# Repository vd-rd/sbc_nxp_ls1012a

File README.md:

# sbc-ls1012a
NXP Layerscape LS1012A

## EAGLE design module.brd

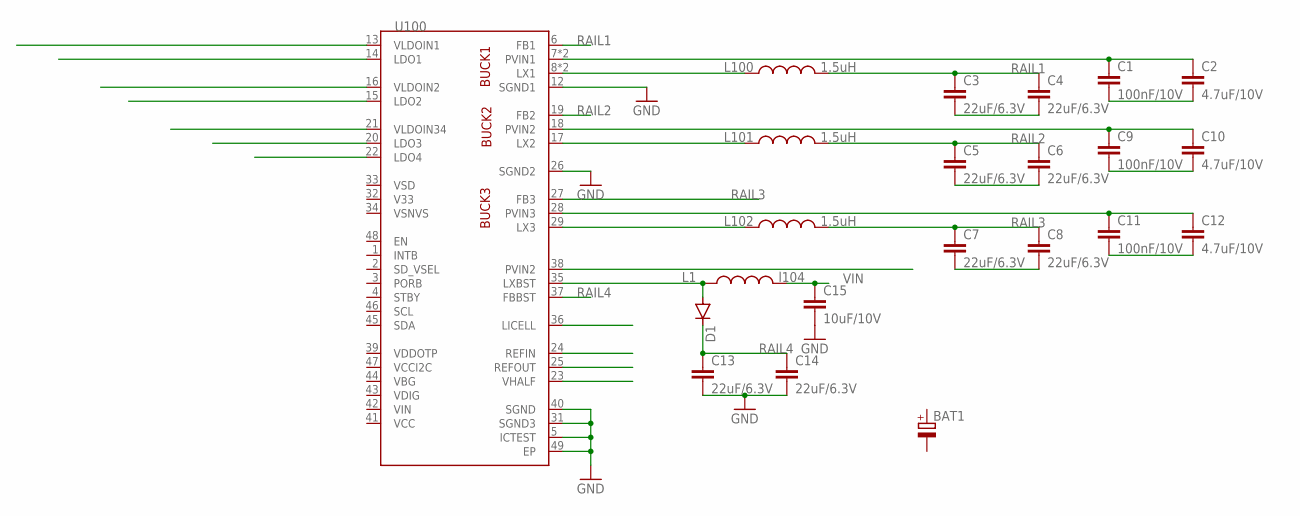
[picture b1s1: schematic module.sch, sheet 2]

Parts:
BAT1: DCK-3R3E224U-E; 621
C1, C9, C11: 100nF/10V; C0603
C2, C10, C12: 4.7uF/10V; C0603
C3, C4, C5, C6, C7, C8, C13, C14: 22uF/6.3V; C0805
C15: 10uF/10V; C0805
D1: DIODE-SOD123; SOD123
L1: l104; INDPM5552X300N
L100, L101, L102: 1.5uH; INDPM5552X300N
U100: MC34VR5100A1EP; QFN50P700X700X90-49T410N

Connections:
GND: C13.2, C14.2, C15.2, U100.5 (ICTEST), U100.12 (SGND1), U100.26 (SGND2), U100.31 (SGND3), U100.40 (SGND), U100.49 (EP)
unnamed: L100.1, U100.8 (LX1), U100.9 (LX1)
unnamed: C1.1, C2.1, U100.7 (PVIN1), U100.10 (PVIN1)
unnamed: L101.1, U100.17 (LX2)
unnamed: L102.1, U100.29 (LX3)
unnamed: D1.A, L1.1, U100.35 (LXBST)
unnamed: C9.1, C10.1, U100.18 (PVIN2)
unnamed: C11.1, C12.1, U100.28 (PVIN3)
unnamed: C3.2, C4.2
unnamed: C1.2, C2.2
unnamed: C11.2, C12.2
unnamed: C7.2, C8.2
unnamed: C5.2, C6.2
unnamed: C9.2, C10.2
RAIL1: C3.1, C4.1, L100.2, U100.6 (FB1)
RAIL2: C5.1, C6.1, L101.2, U100.19 (FB2)
RAIL3: C7.1, C8.1, L102.2, U100.27 (FB3)
RAIL4: C13.1, C14.1, D1.C, U100.37 (FBBST)
VIN: C15.1, L1.2

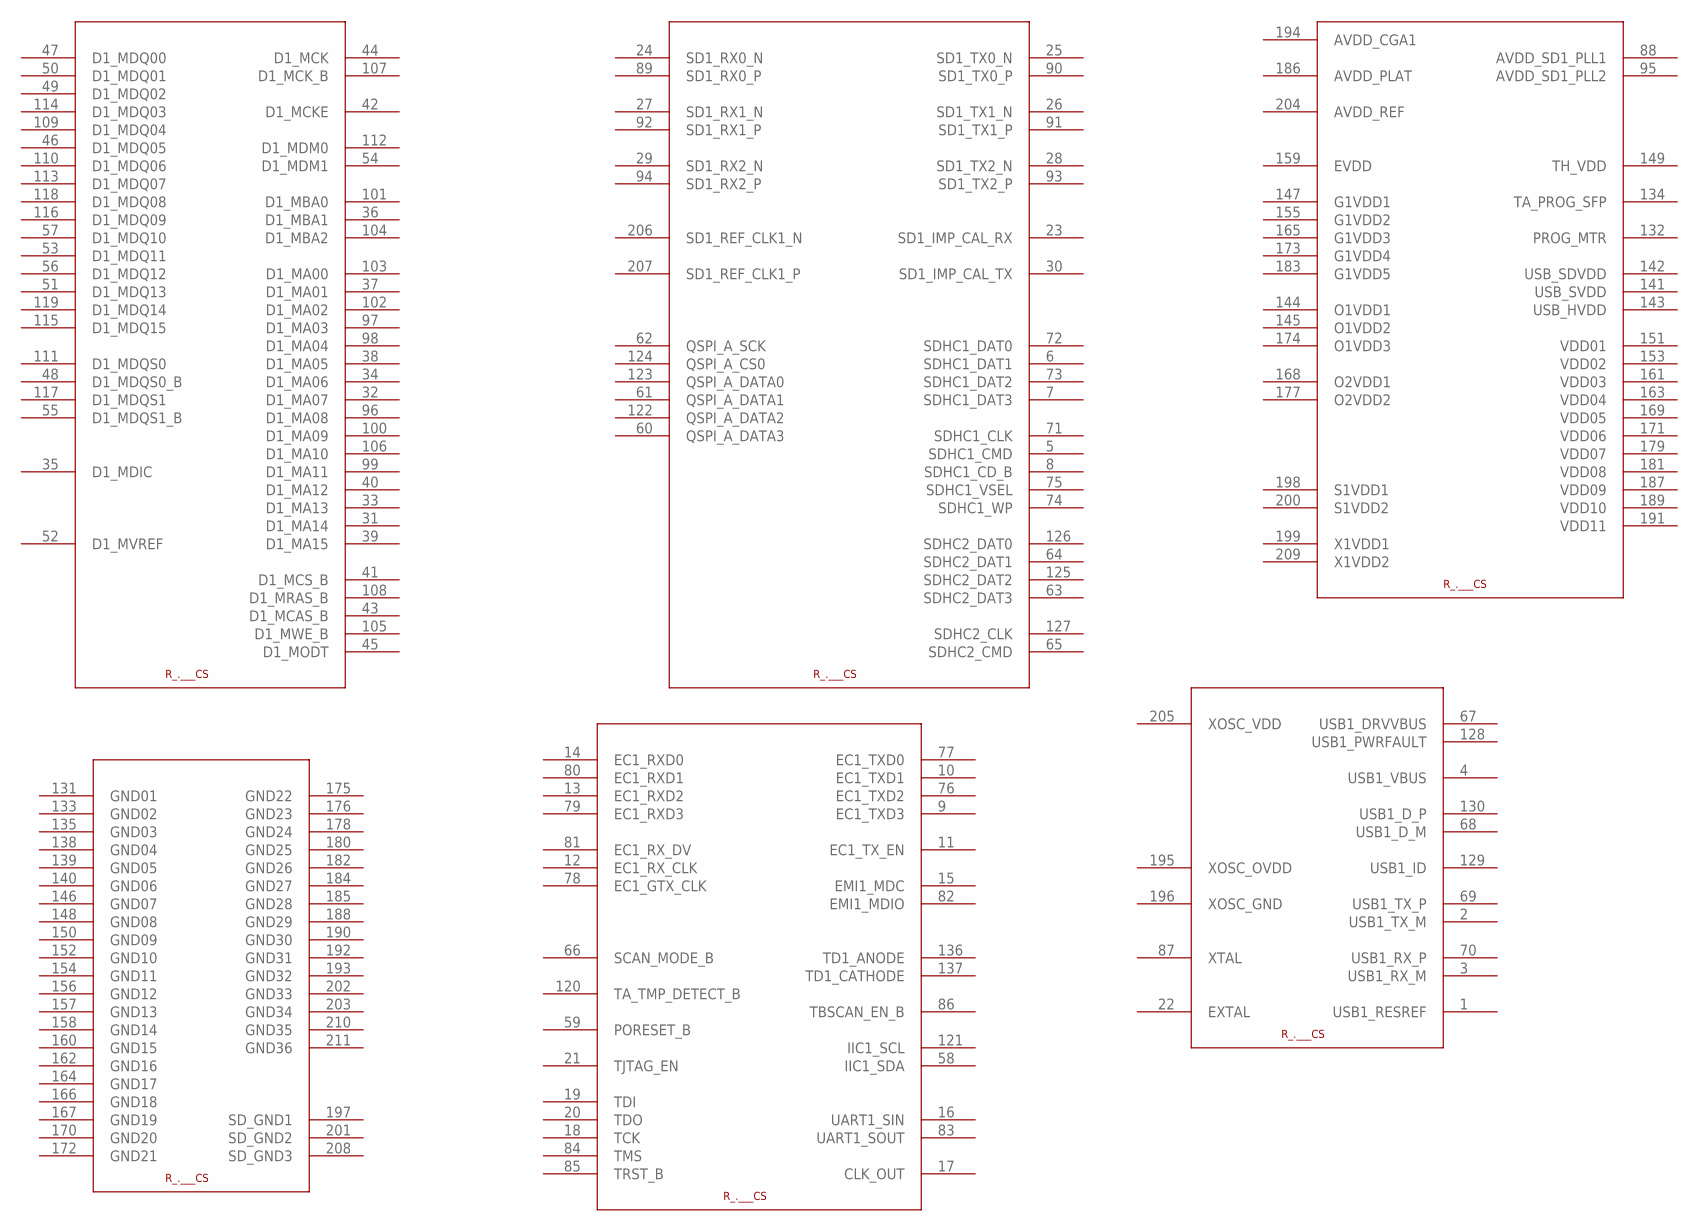
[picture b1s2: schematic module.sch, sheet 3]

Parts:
U3: LS1012ASE7EKA; NXP_LS1012ASE7EKA

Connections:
AVDD_CGA1: U3.194 (AVDD_CGA1)
AVDD_PLAT: U3.186 (AVDD_PLAT)
AVDD_REF: U3.204 (AVDD_REF)
AVDD_SD1_PLL1: U3.88 (AVDD_SD1_PLL1)
AVDD_SD1_PLL2: U3.95 (AVDD_SD1_PLL2)
EVDD: U3.159 (EVDD)
G1VDD1: U3.147 (G1VDD1)
G1VDD2: U3.155 (G1VDD2)
G1VDD3: U3.165 (G1VDD3)
G1VDD4: U3.173 (G1VDD4)
G1VDD5: U3.183 (G1VDD5)
GND01: U3.131 (GND01)
GND02: U3.133 (GND02)
GND03: U3.135 (GND03)
GND04: U3.138 (GND04)
GND05: U3.139 (GND05)
GND06: U3.140 (GND06)
GND07: U3.146 (GND07)
GND08: U3.148 (GND08)
GND09: U3.150 (GND09)
GND10: U3.152 (GND10)
GND11: U3.154 (GND11)
GND12: U3.156 (GND12)
GND13: U3.157 (GND13)
GND14: U3.158 (GND14)
GND15: U3.160 (GND15)
GND16: U3.162 (GND16)
GND17: U3.164 (GND17)
GND18: U3.166 (GND18)
GND19: U3.167 (GND19)
GND20: U3.170 (GND20)
GND21: U3.172 (GND21)
GND22: U3.175 (GND22)
GND23: U3.176 (GND23)
GND24: U3.178 (GND24)
GND25: U3.180 (GND25)
GND26: U3.182 (GND26)
GND27: U3.184 (GND27)
GND28: U3.185 (GND28)
GND29: U3.188 (GND29)
GND30: U3.190 (GND30)
GND31: U3.192 (GND31)
GND32: U3.193 (GND32)
GND33: U3.202 (GND33)
GND34: U3.203 (GND34)
GND35: U3.210 (GND35)
GND36: U3.211 (GND36)
O1VDD1: U3.144 (O1VDD1)
O1VDD2: U3.145 (O1VDD2)
O1VDD3: U3.174 (O1VDD3)
O2VDD1: U3.168 (O2VDD1)
O2VDD2: U3.177 (O2VDD2)
PROG_MTR: U3.132 (PROG_MTR)
S1VDD1: U3.198 (S1VDD1)
S1VDD2: U3.200 (S1VDD2)
SD_GND1: U3.197 (SD_GND1)
SD_GND2: U3.201 (SD_GND2)
SD_GND3: U3.208 (SD_GND3)
TH_VDD: U3.149 (TH_VDD)
USB_HVDD: U3.143 (USB_HVDD)
USB_SDVDD: U3.142 (USB_SDVDD)
USB_SVDD: U3.141 (USB_SVDD)
VDD01: U3.151 (VDD01)
VDD02: U3.153 (VDD02)
VDD03: U3.161 (VDD03)
VDD04: U3.163 (VDD04)
VDD05: U3.169 (VDD05)
VDD06: U3.171 (VDD06)
VDD07: U3.179 (VDD07)
VDD08: U3.181 (VDD08)
VDD09: U3.187 (VDD09)
VDD10: U3.189 (VDD10)
VDD11: U3.191 (VDD11)
X1VDD1: U3.199 (X1VDD1)
X1VDD2: U3.209 (X1VDD2)
XOSC_GND: U3.196 (XOSC_GND)
XOSC_OVDD: U3.195 (XOSC_OVDD)
XOSC_VDD: U3.205 (XOSC_VDD)

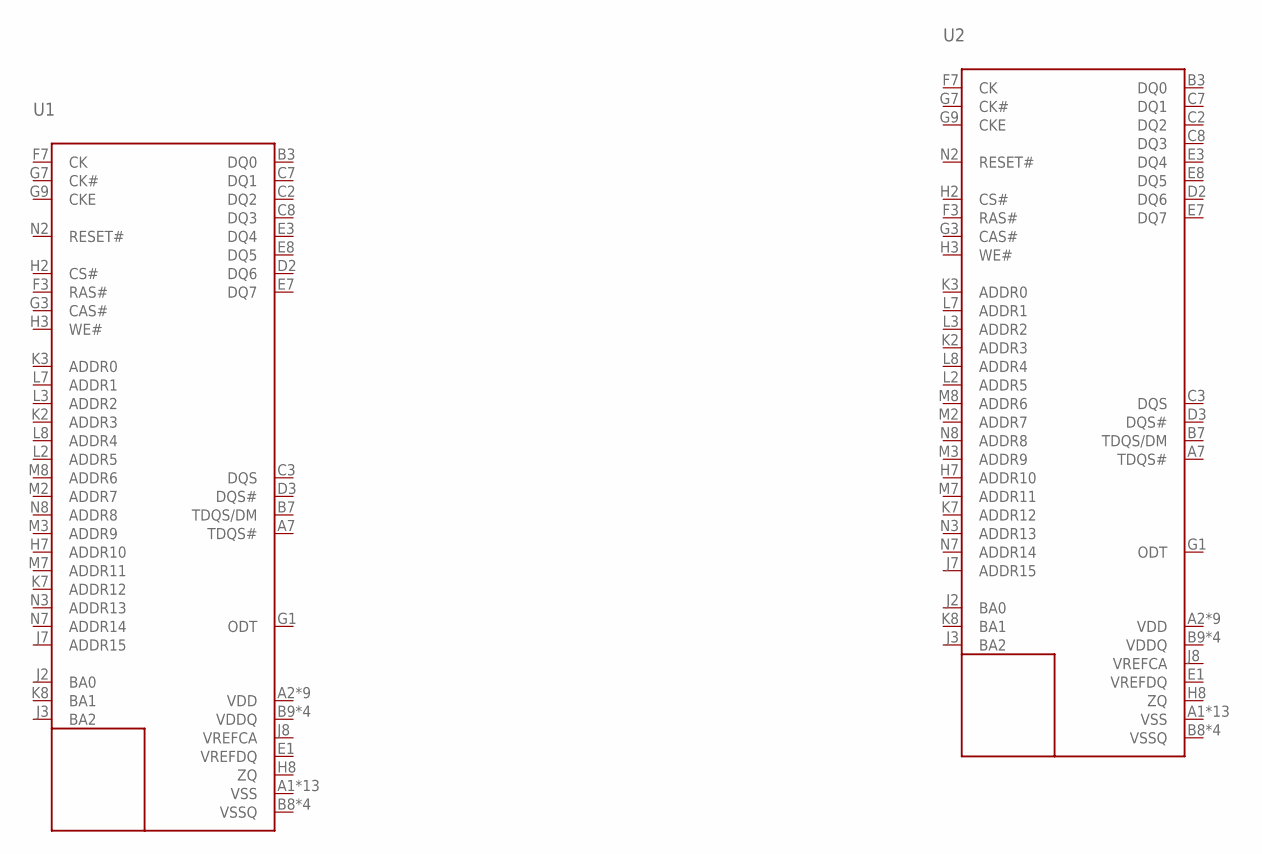
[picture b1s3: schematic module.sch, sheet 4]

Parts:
U1, U2: MT41K512M8; BGA78C80P9X13_1050X800X110

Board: 2 copper layers, 25 parts (0 on the bottom side), 19 nets, no tracks yet.

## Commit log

2021-02-14 project: initial bringup
2021-02-16 project: add pmic
2021-04-27 add gitignore for kicad
2021-04-27 switch project to kicad
2021-04-28 add attributes
2021-04-28 reorg project structure
2021-10-20 updated project
2022-01-03 bump kicad 6
2022-06-29 update project
